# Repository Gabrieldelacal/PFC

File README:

Proyecto Final de Carrera: Control de un Quadcopter.

Hasta ahora se tiene implementado un filtro de kalman de los sensores MPU6050, un modelo del sistema y parcialmente desarrollada la memoria. 

En rubbish se tienen anteriores modelos, descartados todos.

Sources contiene la normativa de la memoria del proyecto y Datasheets del sensor: Especificación y mapa de registros para configurarlo.

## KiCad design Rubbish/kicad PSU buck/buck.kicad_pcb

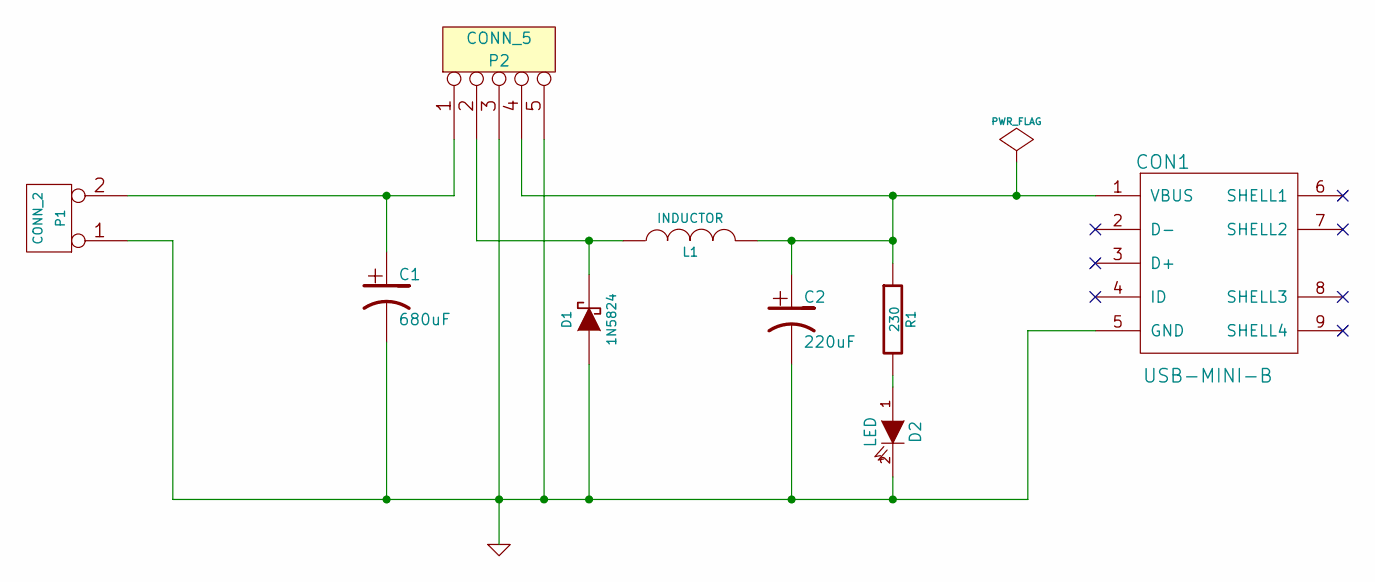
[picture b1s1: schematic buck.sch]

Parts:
C1: 680uF
C2: 220uF
CON1: USB-MINI-B
D1: 1N5824
D2: LED
L1: INDUCTOR
P1: CONN_2
P2: CONN_5
R1: 230

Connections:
unnamed: D1.2 (K), L1.1, P2.2
unnamed: C1.2, C2.2, CON1.5 (GND), D1.1 (A), D2.2 (K), P1.1, P2.3, P2.5
unnamed: D2.1 (A), R1.2
unnamed: C2.1, CON1.1 (VBUS), L1.2, P2.4, R1.1
unnamed: C1.1, P1.2 (PM), P2.1

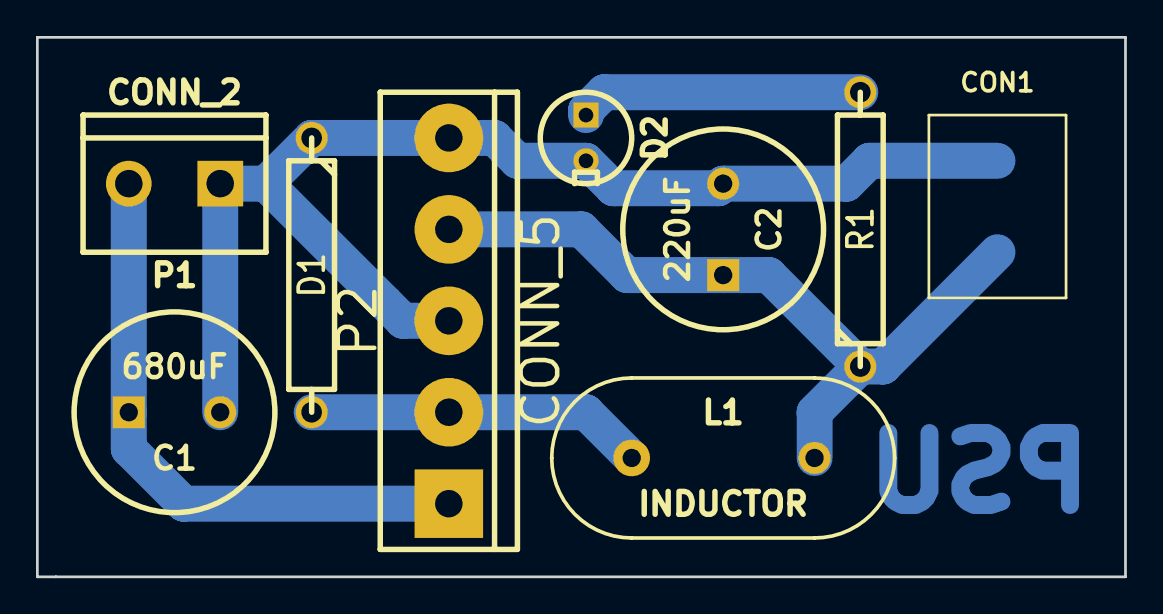
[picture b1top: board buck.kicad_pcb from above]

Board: 2 copper layers, 60.5 x 30.0 mm, 9 parts (0 on the bottom side), 5 nets.

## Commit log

2014-03-30 30_03_14
2014-03-31 31_3_14
2014-04-02 Latex
2014-04-02 Readme
2014-04-04 Latex +changes
2014-04-04 +Sources
2014-04-04 +Others sshfs
2014-04-09 mpu.py
2014-04-09 mpukf.py
2014-04-10 aibo y la galleta
2014-04-10 10_4_14
2014-04-10 images folder
2014-04-10 asdf
2014-04-11 with kalman folder
2014-04-23 with ABC
2014-04-25 more
2014-04-25 discovering
2014-04-27 with sources
2014-05-01 with reduction model
2014-05-02 asdf kalman
2014-05-03 kalman good
2014-05-13 with something more
2014-05-14 lots more
2014-05-16 system almost
2014-05-16 little more
2014-05-21 youyou
2014-05-22 probe
2014-05-23 you you viernes
2014-05-26 adv01
2014-05-27 algo mas
2014-05-27 all in sp
2014-05-28 with spring
2014-05-29 almost
2014-05-29 somethingmore
2014-06-03 almost kalman
2014-06-04 lalailo
2014-06-05 almost...
2014-06-06 sin errores
2014-06-10 implementing Kontr
2014-06-16 casiii
2014-06-16 sin jpg
2014-06-17 con el Registro
2014-06-18 con Izz
2014-06-22 with graphics
2014-06-22 without errors on compiling
2014-06-23 more coments
2014-06-26 with control file
2014-06-30 with a lot more
2014-07-03 with lqr and sampling
2014-07-05 almost done
2014-07-05 almost all
2014-07-06 memoria terminada
2014-07-07 memoria preparada
2014-07-10 All finished
2014-07-14 Postentrega
